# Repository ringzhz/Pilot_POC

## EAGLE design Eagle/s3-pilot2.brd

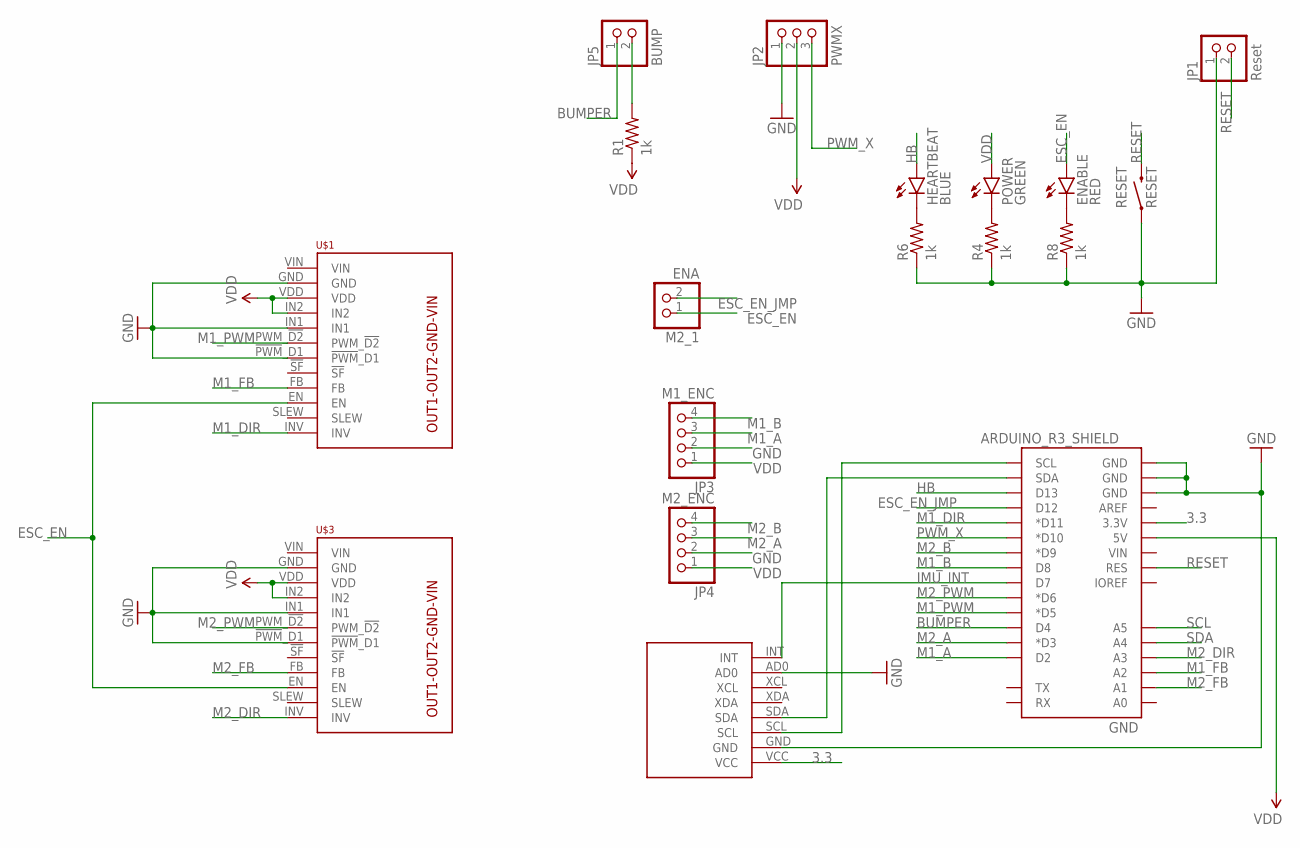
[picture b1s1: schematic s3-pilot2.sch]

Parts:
ENABLE: RED; LED-1206
GND: ARDUINO_R3_SHIELD; UNO_R3_SHIELD
HEARTBEAT: BLUE; LED-1206
JP1: Reset; 1X02
JP2: PWMX; 1X03/90
JP3: M1_ENC; 1X04/90
JP4: M2_ENC; 1X04/90
JP5: BUMP; 1X02/90
M2_1: ENA; 1X02
MPU6050: MPU-6050-BO
POWER: GREEN; LED-1206
R1, R4, R6, R8: 1k; 1206
RESET: RESET; TACTILE_SWITCH_TALL
U$1: M1; MC33926-SINGLE-BO
U$3: M2; MC33926-SINGLE-BO

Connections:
3.3: GND.3.3V, MPU6050.VCC
BUMPER: GND.D4, JP5.1
ESC_EN: ENABLE.A, M2_1.1, U$1.EN, U$3.EN
ESC_EN_JMP: GND.D12, M2_1.2
GND: GND.GND@0 (GND), GND.GND@1 (GND), GND.GND@2 (GND), JP1.1, JP2.1, JP3.2, JP4.2, MPU6050.AD0, MPU6050.GND, R4.1, R6.1, R8.1, RESET.A2 (1), U$1.!PWM!_D1, U$1.GND, U$1.IN1, U$3.!PWM!_D1, U$3.GND, U$3.IN1
HB: GND.D13, HEARTBEAT.A
IMU_INT: GND.D7, MPU6050.INT
M1_A: GND.D2, JP3.3
M1_B: GND.D8, JP3.4
M1_DIR: GND.D11 (*D11), U$1.INV
M1_FB: GND.A2, U$1.FB
M1_PWM: GND.D5 (*D5), U$1.PWM_!D2
M2_A: GND.D3 (*D3), JP4.3
M2_B: GND.D9 (*D9), JP4.4
M2_DIR: GND.A3, U$3.INV
M2_FB: GND.A1, U$3.FB
M2_PWM: GND.D6 (*D6), U$3.PWM_!D2
unnamed: JP5.2, R1.2
unnamed: POWER.C, R4.2
unnamed: ENABLE.C, R8.2
unnamed: HEARTBEAT.C, R6.2
PWM_X: GND.D10 (*D10), JP2.3
RESET: GND.RES, JP1.2, RESET.B2 (2)
SCL: GND.A5, GND.SCL, MPU6050.SCL
SDA: GND.A4, GND.SDA, MPU6050.SDA
VDD: GND.5V, JP2.2, JP3.1, JP4.1, POWER.A, R1.1, U$1.IN2, U$1.VDD, U$3.IN2, U$3.VDD

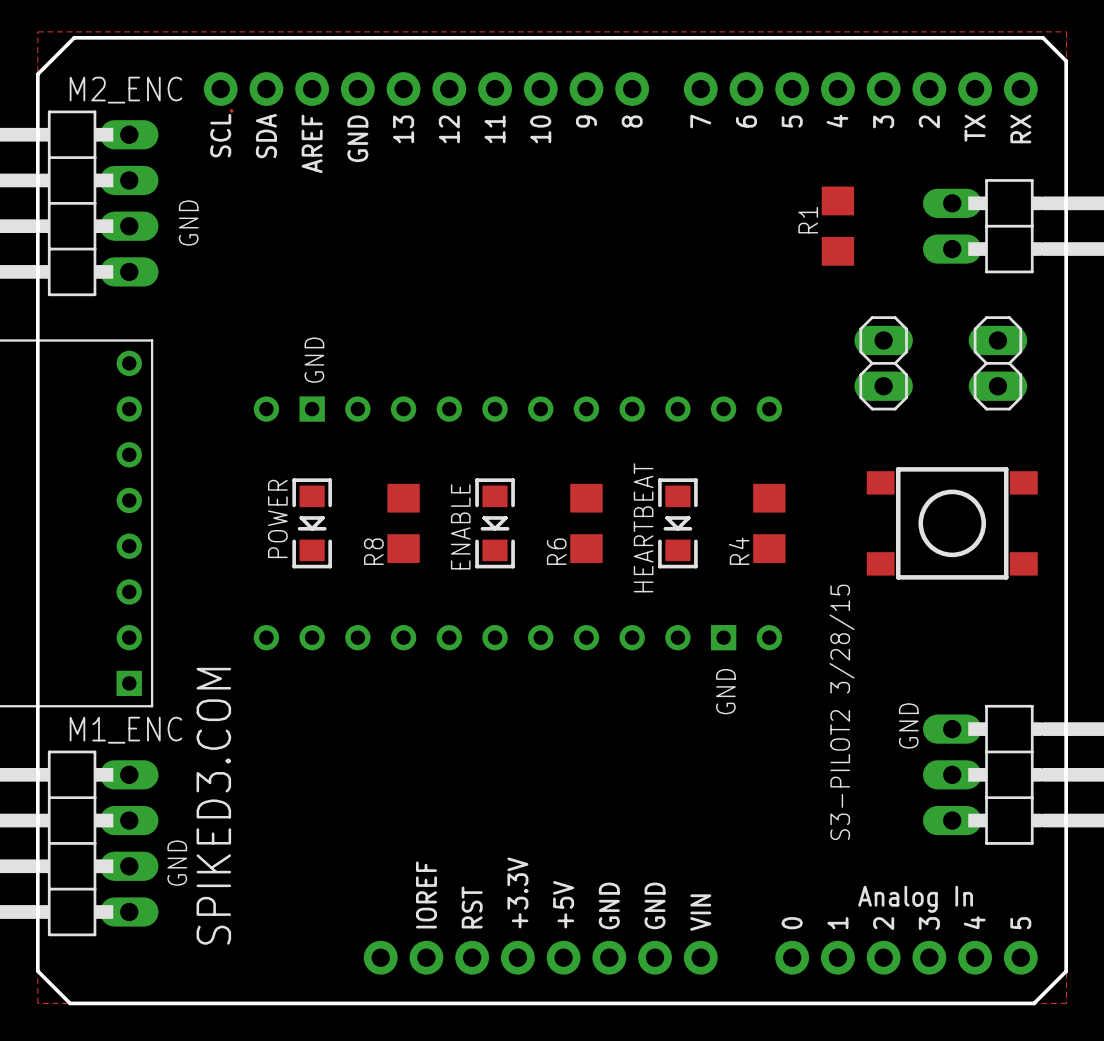
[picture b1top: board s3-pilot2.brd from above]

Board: 2 copper layers, 57.1 x 53.6 mm, 18 parts (0 on the bottom side), 26 nets.

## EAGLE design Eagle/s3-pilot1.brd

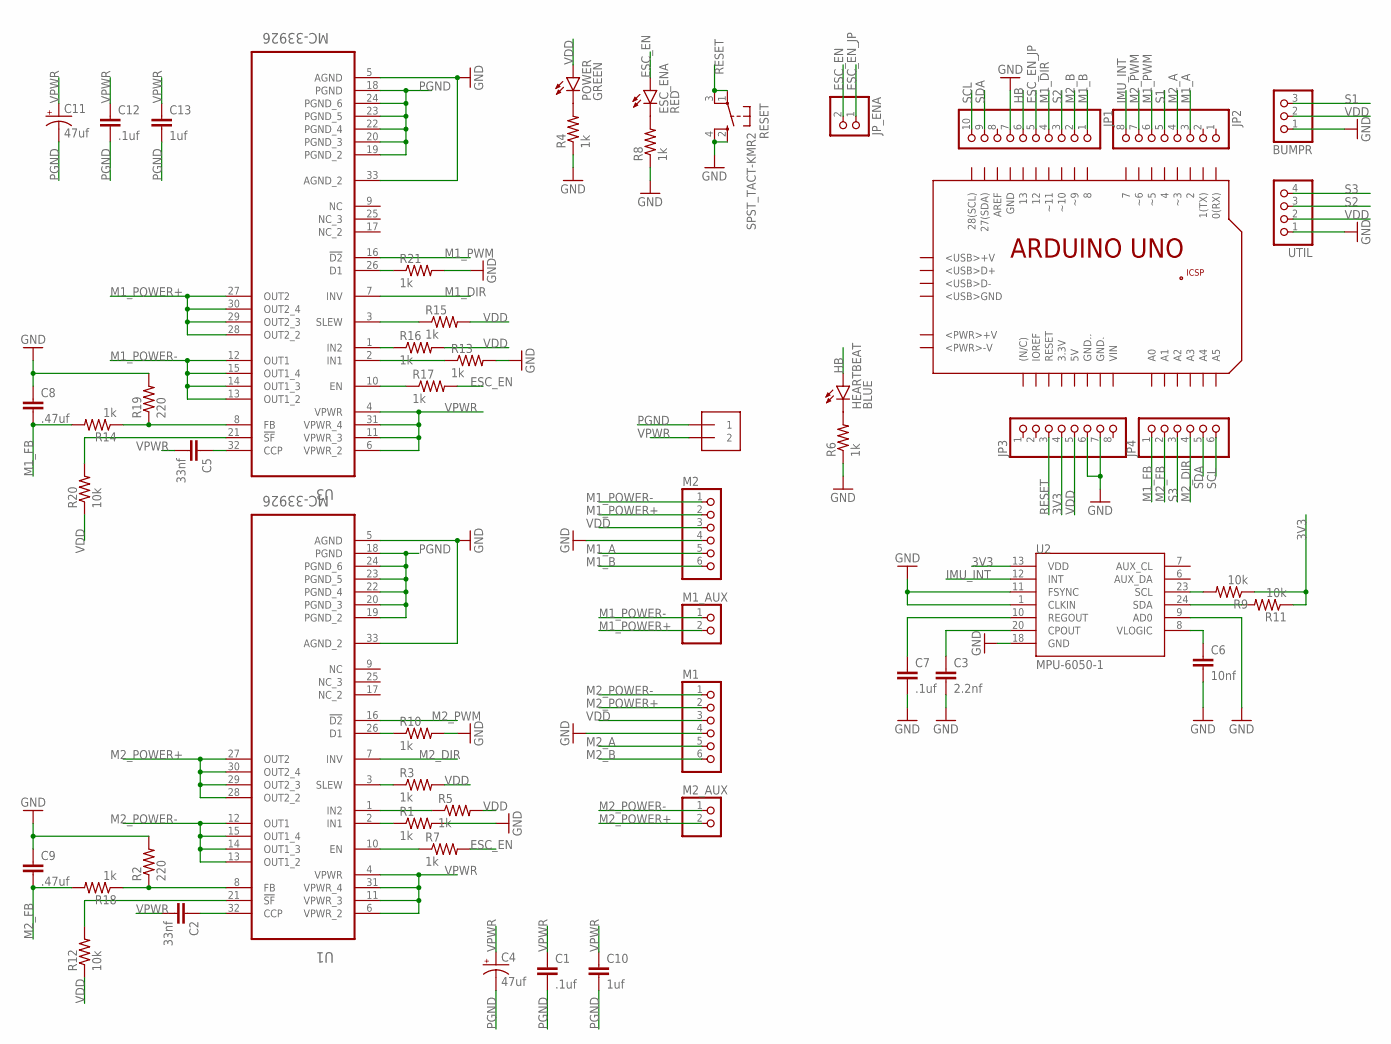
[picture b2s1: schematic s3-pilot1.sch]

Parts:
BUMPR: PINHD-1X3/90; 1X03/90
C1, C7, C12: .1uf; 0805
C2, C5: 33nf; 0805
C3: 2.2nf; 0805
C4, C11: 47uf; PANASONIC_D
C6: 10nf; 0805
C8, C9: .47uf; 0805
C10, C13: 1uf; 0805
ESC_ENA: RED; LED-0603
HEARTBEAT: BLUE; LED-0603
JP1: PINHD-1X10; 1X10
JP2, JP3: PINHD-1X8; 1X08
JP4: PINHD-1X6; 1X06
JP_ENA: PINHD-1X2; 1X02
M1, M2: PINHD-1X6/90; 1X06/90
M1_AUX, M2_AUX: PINHD-1X2/90; 1X02/90
MOTOR_POWER_IN: 1X2-3.5MM
POWER: GREEN; LED-0603
R1, R3, R4, R5, R6, R7, R8, R10, R13, R14, R15, R16, R17, R18, R21: 1k; 0805
R2, R19: 220; 0805
R9, R11, R12, R20: 10k; 0805
RESET: SPST_TACT-KMR2; KMR2
U1, U3: MC-33926; QFN80P800X800X220-33N
U2: MPU-6050-1; QFN-24-4MM2
UTIL: PINHD-1X4/90; 1X04/90

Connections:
3V3: JP3.4, R9.1, R11.1, U2.13 (VDD)
AGND: U1.5 (AGND), U1.33 (AGND_2)
ESC_EN: ESC_ENA.A, JP_ENA.2, R7.2, R17.2
ESC_EN_JP: JP1.5, JP_ENA.1
GND: BUMPR.1, C3.2, C6.2, C7.2, C8.1, C9.1, JP1.7, JP3.6, JP3.7, M1.4, M2.4, R1.2, R2.2, R4.1, R6.1, R8.1, R10.2, R13.2, R19.2, R21.2, RESET.2 (S), RESET.4 (S1), U2.1 (CLKIN), U2.9 (AD0), U2.11 (FSYNC), U2.18 (GND), U3.5 (AGND), U3.33 (AGND_2), UTIL.1
HB: HEARTBEAT.A, JP1.6
IMU_INT: JP2.8, U2.12 (INT)
M1_A: JP2.3, M2.5
M1_B: JP1.1, M2.6
M1_DIR: JP1.4, U3.7 (INV)
M1_FB: C8.2, JP4.1, R14.2
M1_POWER+: M1_AUX.2, M2.2, U3.27 (OUT2), U3.28 (OUT2_2), U3.29 (OUT2_3), U3.30 (OUT2_4)
M1_POWER-: M1_AUX.1, M2.1, U3.12 (OUT1), U3.13 (OUT1_2), U3.14 (OUT1_3), U3.15 (OUT1_4)
M1_PWM: JP2.6, U3.16 (!D2)
M2_A: JP2.4, M1.5
M2_B: JP1.2, M1.6
M2_DIR: JP4.4, U1.7 (INV)
M2_FB: C9.2, JP4.2, R18.2
M2_POWER+: M1.2, M2_AUX.2, U1.27 (OUT2), U1.28 (OUT2_2), U1.29 (OUT2_3), U1.30 (OUT2_4)
M2_POWER-: M1.1, M2_AUX.1, U1.12 (OUT1), U1.13 (OUT1_2), U1.14 (OUT1_3), U1.15 (OUT1_4)
M2_PWM: JP2.7, U1.16 (!D2)
unnamed: R17.1, U3.10 (EN)
unnamed: R10.1, U1.26 (D1)
unnamed: R3.1, U1.3 (SLEW)
unnamed: R15.1, U3.3 (SLEW)
unnamed: C5.1, U3.32 (CCP)
unnamed: C2.1, U1.32 (CCP)
unnamed: R7.1, U1.10 (EN)
unnamed: R5.1, U1.1 (IN2)
unnamed: R1.1, U1.2 (IN1)
unnamed: R16.1, U3.1 (IN2)
unnamed: R21.1, U3.26 (D1)
unnamed: R13.1, U3.2 (IN1)
unnamed: R12.2, U1.21 (!SF)
unnamed: R20.2, U3.21 (!SF)
unnamed: C3.1, U2.20 (CPOUT)
unnamed: C7.1, U2.10 (REGOUT)
unnamed: C6.1, U2.8 (VLOGIC)
unnamed: R2.1, R18.1, U1.8 (FB)
unnamed: POWER.C, R4.2
unnamed: R14.1, R19.1, U3.8 (FB)
unnamed: ESC_ENA.C, R8.2
unnamed: HEARTBEAT.C, R6.2
PGND: C1.2, C4.-, C10.2, C11.-, C12.2, C13.2, MOTOR_POWER_IN.1, U1.18 (PGND), U1.19 (PGND_2), U1.20 (PGND_3), U1.22 (PGND_4), U1.23 (PGND_5), U1.24 (PGND_6), U3.18 (PGND), U3.19 (PGND_2), U3.20 (PGND_3), U3.22 (PGND_4), U3.23 (PGND_5), U3.24 (PGND_6)
RESET: JP3.3, RESET.1, RESET.3 (P1)
S1: BUMPR.3, JP2.5
S2: JP1.3, UTIL.3
S3: JP4.3, UTIL.4
SCL: JP1.10, JP4.6, R9.2, U2.23 (SCL)
SDA: JP1.9, JP4.5, R11.2, U2.24 (SDA)
VDD: BUMPR.2, JP3.5, M1.3, M2.3, POWER.A, R3.2, R5.2, R12.1, R15.2, R16.2, R20.1, UTIL.2
VPWR: C1.1, C2.2, C4.+, C5.2, C10.1, C11.+, C12.1, C13.1, MOTOR_POWER_IN.2, U1.4 (VPWR), U1.6 (VPWR_2), U1.11 (VPWR_3), U1.31 (VPWR_4), U3.4 (VPWR), U3.6 (VPWR_2), U3.11 (VPWR_3), U3.31 (VPWR_4)

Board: 2 copper layers, 53 parts (0 on the bottom side), 52 nets, no tracks yet.

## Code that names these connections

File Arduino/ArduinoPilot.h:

#ifndef __ArduinoPilot__H
#define __ArduinoPilot__H

// digital pins
const int LED = 13;

// motor pins
<<<<<<< HEAD
const int M1_PWM = 5;
const int M2_PWM = 6;
const int M1_DIR = 11;
const int M2_DIR = 17;
=======
// +++ now-esc version
//const int M1_PWM = 5;
//const int M2_PWM = 6;
//const int M1_DIR = 11;
//const int M2_DIR = 10;
>>>>>>> no-esc

/*  hardcoded in PilotMotor!
#define M1_A 2	// interrupt 0 = pin 2
#define M1_B 8
#define M2_A 3	// interrupt 1 = pin 3
#define M2_B 9
*/

const int ESC_EN = 12;

#define toggle(X) digitalWrite(X,!digitalRead(X))

// analog pins
const int M1_FB = 0;
const int M2_FB = 1;

//#define SDA 4
//#define SCL 5

typedef struct {
	int ticksPerRevolution;
	float wheelDiameter;
	float wheelBase;
	float EncoderScalar;	// calculated
} Geometry;

#endif

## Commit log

2015-01-20 initial
2015-01-22 Working decoder
2015-01-29 . working well, except Arduino has a pause when it receives a message?
2015-02-01 maxmavin board sent to oshpark 01/31/2015
2015-02-05 working 2 way needs to be actual implementation now uses softSerial on pin 6 to communicate debugging info to Bus Blaster UART monitor
2015-02-09 working wpf 3d (not program but view) before change to helix3D
2015-02-12 changed timing a little trying to work out msgs out of sequence or dropped data issue I think it will require time stamping and check sums ultimately
2015-02-17 changed to PilotMotor class did some kludging on interrupts to make work
2015-02-27 pilot board v2 - breakout boards as daughter this version sent to OSH 2/27/15
2015-03-16 chkpt before changing ISR around - it is not working well - too fast?
2015-03-22 work with David, found wiring problem both motors working, now needs code cleaned up / implemented
2015-03-22 cleanup / implement still seems like some interrupt probs, but otherwise, in the ballpark
2015-03-23 odometry code correct I still want to read digital pins the fast way
2015-03-25 moved xbee to softserial on 10,11 since esc not used added reverse consideration in getTacho - seems to be ok for now working on lidarbot with RC drive need to update bridge and winViz to new serial 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
2015-03-26 working basically, still need to correct x/y/h stuff (as usual) added remote reset jumper for arduino to sch
2015-03-28 fixed up axi, made you_tube movie need to merge - then probably several branches -> lidar, pibot-david, pibot-mikep
2015-03-28 working with david
2015-03-29 work session with David verified ESC work - problem was buttons on breadboard verify a few updates and eagle, then re-order Code needs to be split / merged / something to deal with various situations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
2015-03-29 remove dynamic files
2015-03-29 eagle updates - brd not complete
2015-03-29 touch up
2015-03-29 moved eagle to different repro
2015-03-29 refactor
2015-03-31 final new message format (i hope)
2015-04-01 changed sub topic to cmd/robot1
2015-04-01 seems to b ok
2015-04-02 moved XBee to 1/2 and swapped on arduino xbee shield you must switch between USB and serial for coding/wireless - but it works good rename dir to make it 'arduino IDE' compatible
2015-04-02 working with gps data but dropping a lot of bytes, need to do some experiments with baud rates
2015-04-02 testing gps on softserial
2015-04-03 major refactor
2015-04-03 ready for testing
2015-04-03 add/used flags for what is enabled
2015-04-06 fairly significant cleanup attempt to add interrupt driven gyro - but didnt work so fell back on interval for now (may be fine as is)
2015-04-07 gyro in, kalman in - but needs tweaking/testing!! waiting on boards and motors :|
2015-04-08 huge update on new branch can not get it to link though - multiple definitions on mpu
2015-04-09 cleaning up still getting over flows even though I slowed down dmp something still not quite right in loop but - end to end, rotate gyro - shows up in winViz :)
2015-04-09 woke up at 3am. decided to reset fifo every read. worked perfectly. Up'd sample rate back to 100 times / sec probably should recalc pose on every interrupt now, encoder and mpu
2015-04-11 ckpt a lot of changes
2015-04-11 ready for powered motor test quite a bit of the API done running out of room :(
2015-04-11 cleanup before changing log to DBGLOG
2015-04-11 cleaned up the cleanup
2015-04-12 working next rotate
2015-04-13 I hate arduino (the software) Gave up and finally merged everything into 1 file
2015-04-13 another reorg now that it is compiling. Arduino does things differently bug heading reset to non 0 heading still broke
2015-04-18 half way through some changes
2015-04-18 finally working again. memory is getting tight. ended up reverting back to visual micro and arduino 1.6.1 <- important
2015-04-19 bumper working (with pin chnges)
2015-04-19 made robot1 a const char *
2015-04-20 added Pid, not fully implemented
2015-04-21 code that is there is working (as far as I know) still need to finish up regulation stuff
2015-04-23 still working on PID. power v speed is confusing as hell. If I dont get it soon I might just rip it all out and start again. The hex file is not current. Still trying to figure out how to make visual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
2015-04-24 started re-write of motor control. realistically it will take a couple of weeks at best just to get rudimentary functions working again. Totally based on LeJOS (and all their hard to figure out varia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
2015-04-24 a little cleanup
2015-04-25 fixed heading reset
2015-04-25 making progress, but I am out of memory. I have to comment out parts of code to add debugging. This might be time to get rid of the pub/sub protocol and let the bridge handle that, but realistically 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
2015-04-27 motors are moving again anyhow. Still having problems find all bugs. Part might be the NXT code assumes 360 ticks per rotation, we have 60. I am also not completely sure what #s are passed as Acceler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
2015-04-27 Need to redo the tacho code. motor regulation moved into pilot regulation and not as a separate task. This will require changing how tachometers are used. Otherwise, still making tiny steps, but not 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
2015-05-01 OMFG, slow acceleration is working, I havent tried others. It has problems after acceleration, but it is the closest it has ever been.
2015-05-01 I give. ripping it all out.
2015-05-01 Well the code is ripped out, but Arduino IDE cant even download the code anymore without unplugging the arduino everytime. Has to be some of the worst software I have used. I will not say the worst, 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
2015-05-03 really really giving up. I cant even make simple pid work. No pid for now and maybe I can find a programmer to add it in later.
2015-05-03 actually kind of working :|
2015-05-04 branching for pid via array w/update
2015-05-04 branch done
2015-05-04 Implemented about all I can without a chassis. Going to disassem current LidarBot.
2015-05-06 I'm going to call it done (except heading stuff/needs chassis). about the 5th time now.
2015-05-08 License
2015-05-09 lots of cleanup, got sketch back down under 31k added calibration values cmd, but need more testing.
2015-05-09 Calibration And Rotation
2015-05-10 So, there is some magic sequence you have to do - seems like it you send calibration data after it is settled, the gyro recalibrate, but my code doesnt really handle that. But it is kinda close I thi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
2015-05-10 rotate working better - it should probably be setting tgtVelocity and not power, so motor regulator PID handles the smaller values. Important: the gyro init sequence has to be manually done if you ar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
2015-05-12 makefile supported
2015-05-13 tried cleaning code again. Arduino is just too crappy to do this the right way. So, back to same ole #include code route.
2015-05-13 make file copies latest hex
2015-05-13 noted makefile restriction
2015-05-16 demo prep
2015-05-20 commit before tuning PIDs some. Test programs are working good.
2015-05-26 reduce code size - drop pilot functions for now
2015-05-30 deleted a lot of commented out code quick test and target velocity/actual is wrong, but the new congif stuff seems ok will fix later, falling asleep
2015-05-30 oops
2015-05-30 Added pin power to hb
2015-06-08 added in heading stop for turning
2015-06-10 added more PID vars for plotting
2015-06-10 fixed PID Lots of other changes Serial still locks up often, have to reset arduino
2015-06-12 Pump up some dataRead rates. Do weird stuff with Velocity Measurement
2015-06-12 cleanup. It has a consistent start up issue where it takes off full throttle, but on some occasions, it does not I think this is related to zero'ing out variables at the wrong time HeadingInRange is 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
2015-06-14 fix found by jesseg for how I was doing PID wrong. working good (#s are .3,.9,.0025 atm) can go back to heading stuff now
2015-06-20 Pleaseenter the commit message for your changes. Lines starting deleted header file
2015-06-21 from Pi
2015-06-22 Clean up. simplified. Will switch to a new name and do a significant rewrite next version.
2015-07-06 refactor - moved all into 1 file to avoid Arduino issues, dropped vs support (sucked anyhow) quick test seems code is as good as previous version.

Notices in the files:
parts and their libraries:
SparkFun-Capacitors: Licensing: Creative Commons ShareAlike 4.0 International - https://creativecommons.org/licenses/by-sa/4.0
